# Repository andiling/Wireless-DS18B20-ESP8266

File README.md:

# ---->Moved to Domochip/Wireless-DS18B20-Bus<----
----> https://github.com/Domochip/Wireless-DS18B20-Bus <----

# WirelessDS18B20

This project use an ESP8266 and some DS18B20 sensors on a 1-Wire bus to provide temperatures in JSON format (Jeedom compatible).

The global idea of this project is that any system (like Jeedom) that's able to do an HTTP GET request and interpret JSON will get list of DS18B20 ROMcode available on buses or current temperature of a DS18B20 sensor.

## Build your 1-Wire bus

In order to get a wide 1-Wire bus (one that cover a house), Dallas provides some recommendations into their application note AN148.

This project use the Improved Interface bellow that is able to support a 200m bus:

This one requires a pin for reading the bus state and another one as output to drive the bus low : I named it the "Dual Pin OneWire"

**Warning : If you build a large 1 Wire bus inside your house, keep in mind that some high voltage may appear on this one by induction. You need to have a good knowledge about electricity and associated risks!!!**

## Build your WirelessDS18B20

All files are inside schematic subfolder and has been designed with KiCad

### Schematic

### PCB

### Code/Compile

Source code can be compiled for :

- ESP-01 : Pin usage is fixed like in schematic.
- other ESP8266 models : 1-Wire buses pins can be configured through the configuration webpage

In order to compile you first need to run PowerShell script which is in htmlToCppHeader folder.
This one compress and then convert into code (PROGMEM variables) the webpages files (into data folder)

## Run

### First Boot

During First Boot, the ESP boot in Access Point Mode to allow you configuration

- Network SSID : `WirelessDS18B20`
- Password : `PasswordDS18B20`
- ESP IP : `192.168.4.1`

Connect to this network and then configure it.

### Configuration

WirelessDS18B20 offers you some webpages in order to configure it :

- `http://IP/` return you the current status of the module :

- `http://IP/config` allows you to change configuration (Wifi and 1-Wire buses (only non-ESP01)) :

- **ssid & password** : IDs of your Wifi Network
- **hostname** : name of ESP on the network
- **IP,GW,NetMask,DNS1&2** : Fixed IP configuration
- **number of OneWire buses** : number of OneWire buses...
- **buses pin numbers** : pins for each oneWire buses (2 pins per OW bus)

- `http://IP/fw` allows you to flash a new firmware version :

### Rescue Mode

If you lost access to your WirelessDS18B20, you can `reset it` (reset button or power off) and during the 5 first seconds, `press the "Rescue Mode" button` to start it with default config (like during First Boot).

## Use it

### Basics

Usage (answers are in JSON format):

- `http://IP/getList?bus=0` will return list of DS18B20 ROMCodes available on the 1-Wire bus number 0
- `http://IP/getTemp?bus=0&ROMCode=0A1B2C3D4E5F6071` will return simple JSON with temperature from the sensor

### With Jeedom

> Memento : Jeedom is an innovative home automation system that can be found at <http://jeedom.com>

For this configuration you need the *Script* plugin installed from the market :

Go to script plugin then add a new equipment:

Name it :

Set refresh time (every minutes in my case) :

Then into command tab, add a script command :

Then set it up with :

- command name : Temperature
- script type : JSON
- request : Temperature (JSON tag name)
- URL : <http://***IP***/getTemp?bus=***0***&ROMCode=***0A1B2C3D4E5F6071***>
- Unit : °C

Now you're done and should get something like this :

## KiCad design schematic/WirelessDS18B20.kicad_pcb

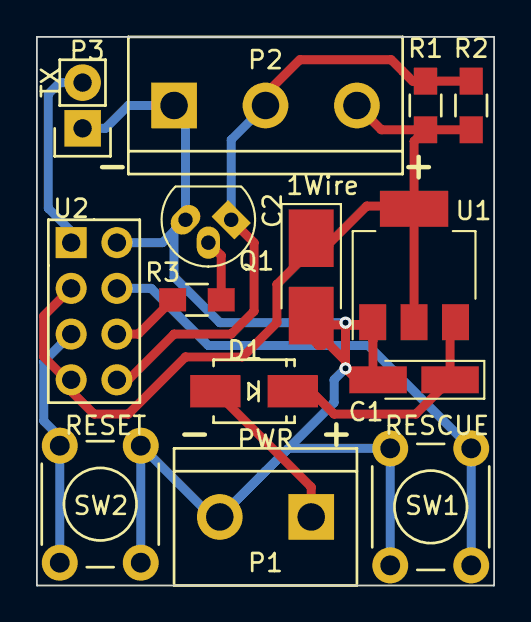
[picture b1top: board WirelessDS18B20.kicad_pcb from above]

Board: 2 copper layers, 25.4 x 30.5 mm, 14 parts (0 on the bottom side), 10 nets.

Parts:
C1: 10uF; CP_Tantalum_Case-A_EIA-3216-18_Hand
C2: 100uF; CP_Tantalum_Case-B_EIA-3528-21_Hand
D1: SS34; SMA_Handsoldering_Custom
P1: Power Connector; bornier2
P2: 1-Wire Bus; bornier3
P3: SERIAL_TX; Pin_Header_Straight_1x02
Q1: BS170; TO-92_Molded_Narrow_Oval
R1, R2, R3: 2.2K; R_0805_HandSoldering
SW1: RESCUE_MODE; SW_PUSH_6mm
SW2: RESET; SW_PUSH_6mm
U1: AMS1117 3.3; SOT-223
U2: ESP-01

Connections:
GND: C1.2, C2.2, P1.2, P2.1, P3.1, Q1.3, SW1.2, SW2.2, U1.1, U2.2
unnamed: C1.1, D1.1, U1.3
unnamed: D1.2, P1.1
unnamed: P2.2, Q1.1, R1.2, R2.2, U2.8
unnamed: P3.2, U2.1
unnamed: Q1.2, R3.2
unnamed: R3.1, U2.6
unnamed: SW1.1, U2.4
unnamed: SW2.1, U2.5
VCC: C2.1, P2.3, R1.1, R2.1, U1.2, U1.4, U2.3, U2.7

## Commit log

2016-07-06 v0.8
    Created main structure and first functionnal source
2016-07-06 v0.9
    Improve memory usage and HTTP request handling
2016-07-06 v1.1
    For larger 1-Wire bus, Improved Bus Interface is required. I named it
    Dual Pin 1-Wire
2016-07-06 v1.2
    Implement ESP-01 compilation constraint
2016-08-02 Add Schematic
2016-08-08 Update Schematic
2016-08-22 Fix no Bus for ESP-01
2016-08-23 Improve loadConfig and print IP while starting
2016-08-23 Fix WiFi never connect after changes
2017-02-17 Implement Config class
    Switch from configuration global variables to Config class (that is
    stored into EEPROM)
2017-02-17 Improve performance for browser other than IE
    Use WiFiClient.write instead of WiFiClient.print (send multyple bytes
    per network packet...)
2017-02-17 Use dynamic WebPage store in SPIFFS
    Switch to ESPWebServer, return WebPage (using JQuery) stored in SPIFFS
    and minimize content generated by ESP to simple JSON datas
2017-02-17 return to WiFiServer for memory improvement
2017-02-17 V2.0 Very big split into classes
    Program splitted into classes and WebPages improvement
2017-02-20 WebDS18B20Buses class and SendHTTPShortAnswer
    WebDS18B20Buses is a class to manage a "collection" of WebDS18B20Bus
    SendHTTPShortAnswer has been added to WebCore in order to factorise HTTP
    header code lines everywhere
2017-02-20 Memory improvment, Web optimization
    getconfig has been replaced by status webpage (config is in config).
    SendHTTPShortAnswer became SendHTTPResponse.
    String has been used back to generate JSON code but reserve function has
    been used to reduce heap leak.
    etc... :-)
2017-02-21 V2.2 include Webpages into Code
    Native webpages are now include in code (simpler for firmware update)
    and so a developper mode that still use SPIFFS is implement for
    developping
2017-02-22 V2.3 Config DefaultValue and rework on FindParam
2017-02-22 BugFix
2017-02-22 Reduce code while not in DEV mode
2017-02-23 init Config and better fw validation
2017-03-09 Update Schematic (PCB now Provided)
2017-03-09 Update README.md
    describe new interface and update schematic and PCB
2017-03-30 few optimization
2017-03-30 Update WebFiles
2017-03-31 Update Schematic
    Addition of power diode against bad connection + reduce board size
2017-03-31 Add Bill of Material for hobbyist
2017-05-03 v2.3.5 - Improve WiFi management
    Improve WiFi management
    correct IE bug on fw pages
    reduce first delay to 200
2017-05-03 Improve Status
2017-05-18 Update Color
2017-05-18 Wifi code goes up
2017-05-18 Set Serial speed to 115200
2017-06-13 Add OpenSCAD box for WirelessDS18B20
    Version Number corespond to PCB version number
2017-10-11 V3.0
    switch to ESPAsyncWebServer from me-no-dev
    lot of improvement
2017-10-12 Correct Config param size check
2017-10-12 Switch to JQuery CDN by default (3.2.1)
2017-10-12 Add Expires:0 header
2017-10-31 Improve Schematic (update KiCad to 4.0.7)
2017-10-31 Update Screenshots for firmware V3
2017-10-31 Add compiled version (1M 64KSpiffs)
2017-11-26 Readme update
